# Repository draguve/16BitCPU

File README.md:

A 16 Bit CPU Schematic

## Instruction Set

It can be found [here](https://docs.google.com/spreadsheets/d/1bDObkBc0xerhLb_7aUqUZHJFpincPKz191_meNZrJVs/edit?usp=sharing)

The cpu has 2 Resgisters , an Instruction Register,A Memory Access Register and a simple adder/subtractor and 8Kb RAM and ROM 

*Overview*

*Clock*

*Register*

*Swap-Register*

*ALU*

*Program Counter*

*RAM*

*Control Unit*

*Instruction Register*

*LEDs*

*Display*

*Power*

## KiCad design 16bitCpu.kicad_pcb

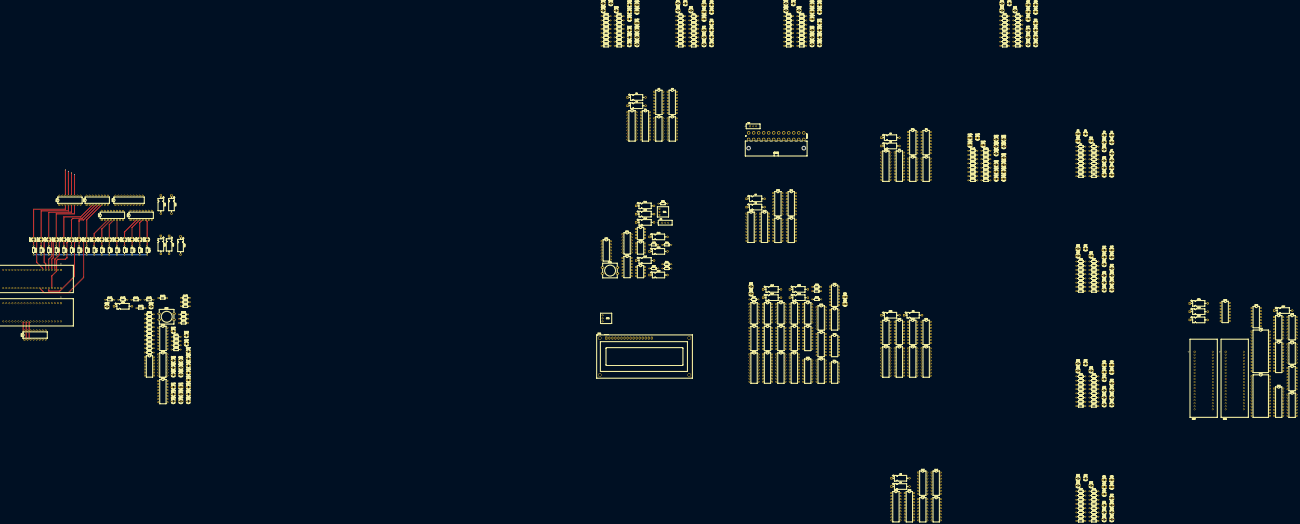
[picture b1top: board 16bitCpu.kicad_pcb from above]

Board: 2 copper layers, 509 parts (0 on the bottom side), 455 nets.

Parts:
C1, C2, C3, C4, C5, C6, C7, C8, C9, C10, C14, C16, C17, C18, C19, C20, C21, C22, C23, C24, C25, C26, C27, C28, C29, C30, C31: 0.1uF; CP_Axial_L10.0mm_D4.5mm_P15.00mm_Horizontal
C11, C13, C15: 0.01uF; CP_Axial_L10.0mm_D4.5mm_P15.00mm_Horizontal
C12: 1uF; CP_Axial_L10.0mm_D4.5mm_P15.00mm_Horizontal
D1, D2, D3, D4, D5, D6, D7, D8, D9, D10, D11, D12, D13, D14, D15, D16, D17, D18, D19, D20, D21, D22, D23, D24, D25, D26, D27, D28, D29, D30, D31, D32, D33, D34, D35, D36, D37, D38, D39, D40, D41, D42, D43, D44, D45, D46, D47, D48, D49, D50, D51, D52, D53, D54, D55, D56, D57, D58, D59, D60, D61, D62, D63, D64, D65, D66, D67, D68, D69, D70, D71, D72, D73, D74, D75, D76, D77, D78, D79, D80, D81, D82, D83, D84, D85, D86, D87, D88, D89, D90, D91, D92, D93, D94, D95, D96, D97, D98, D99, D100, D101, D102, D103, D104, D105, D106, D107, D108, D109, D110, D111, D112, D113, D114, D115, D116, D117, D118, D119, D120, D121, D122, D123, D124, D125, D126, D127, D128, D129, D130, D131, D132, D133, D134, D135, D136, D137, D138, D139, D140, D141, D142, D143, D144, D145, D146, D147, D148, D149, D150, D151, D152, D153, D154, D155, D156, D157, D158, D159, D160, D161, D162, D163, D164, D165, D166, D167, D168, D169, D170, D171, D172, D173, D174, D175, D176, D177, D178, D179, D180, D181, D182, D183, D184, D185, D186, D187, D188, D189: LED; LED_D3.0mm
DS1: WC1602A
J1: ATX24RH; ATX24_RIGHT_ANGLE
R1, R2, R3, R4, R5, R6, R7, R8, R9, R10, R11, R12, R13, R14, R15, R16, R17, R18, R19, R20, R21, R22, R23, R24, R25, R26, R27, R28, R29, R30, R31, R32, R33, R34, R35, R36, R37, R38, R39, R40, R41, R42, R43, R44, R45, R46, R47, R48, R49, R50, R51, R52, R53, R54, R55, R56, R57, R58, R59, R60, R61, R62, R63, R64, R65, R66, R67, R68, R69, R70, R71, R72, R73, R74, R75, R76, R77, R78, R79, R80, R87, R88, R89, R90, R91, R92, R93, R94, R95, R96, R97, R98, R99, R100, R101, R102, R103, R104, R105, R106, R107, R108, R109, R110, R111, R112, R113, R114, R115, R116, R117, R118, R119, R120, R121, R122, R123, R124, R125, R126, R127, R128, R129, R130, R131, R132, R133, R134, R135, R136, R137, R138, R139, R140, R141, R142, R143, R144, R145, R146, R147, R148, R149, R150, R151, R152, R153, R154, R155, R156, R157, R158, R159, R160, R161, R162, R163, R164, R165, R166, R167, R168, R169, R170, R172, R173, R174, R175, R176, R177, R178, R179, R180, R181, R182, R183, R184, R185, R186, R187, R188, R189, R190, R191, R192, R193, R194, R195, R196: 220; R_Axial_DIN0204_L3.6mm_D1.6mm_P7.62mm_Horizontal
R81, R82, R83, R85, R86, R171: 1K; R_Axial_DIN0204_L3.6mm_D1.6mm_P7.62mm_Horizontal
R84: 1M; R_Axial_DIN0204_L3.6mm_D1.6mm_P7.62mm_Horizontal
RV1: 1M; Potentiometer-5.5mm
RV2: 10K; Potentiometer-5.5mm
SW1: SW_Push; SW_PUSH-12mm
SW2: SW_SPDT; SW_MINI-SPDT-SW
SW3: SW_Push-Switch; SW_PUSH-12mm
SW4: SW_SPDT-Switch; SW_MINI-SPDT-SW
U1, U4, U7, U10, U13, U14, U19, U22, U25, U28, U29, U32, U39, U52, U54, U59, U65, U66, U69: 74LS245; DIP-20_W7.62mm
U2, U3, U5, U6, U8, U9, U11, U12, U20, U21, U23, U24, U26, U27, U30, U31, U57, U61, U62, U63, U64, U67, U68, U70, U71: 74LS173; DIP-16_W7.62mm
U15, U16, U17, U18: 74LS161; DIP-16_W7.62mm
U33, U37, U38: LMC555xN; DIP-8_W7.62mm
U34: 74LS04; DIP-14_W7.62mm
U35: 74LS08; DIP-14_W7.62mm
U36: 74LS32; DIP-14_W7.62mm
U40, U44, U47, U48: 74LS00; DIP-14_W7.62mm
U41, U42, U43, U45: 74LS86; DIP-14_W7.62mm
U46: 74HC02; DIP-14_W7.62mm
U49, U51, U55, U58: 74LS283; DIP-16_W7.62mm
U50, U53, U56, U60: 74LS85; DIP-16_W7.62mm
U72, U78: 74HC04; DIP-14_W7.62mm
U73: 74HC00; DIP-14_W7.62mm
U74, U75, U81, U82: AT28C256; ZIF-AT28C64B-15PU
U76, U77: AS6C62256A; DIP-28_W15.24mm
U79: 7400; DIP-14_W7.62mm
U80: 74LS161-74xx; DIP-16_W7.62mm
U83, U84, U85: 74LS138; DIP-16_W7.62mm

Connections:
+5V: C1.1, C2.1, C3.1, C4.1, C5.1, C6.1, C7.1, C8.1, C9.1, C10.1, C16.1, C17.1, C18.1, C19.1, C20.1, C21.1, C22.1, C23.1, C24.1, C25.1, C26.1, C27.1, C28.1, C29.1, C30.1, C31.1, DS1.2, DS1.15, J1.4, R81.1, R83.1, R84.1, R85.1, R86.1, SW3.2, U1.1, U1.20, U2.16, U3.16, U4.1, U4.20, U5.16, U6.16, U7.1, U7.20, U8.16, U9.16, U10.1, U10.20, U11.16, U12.16, U13.1, U13.20, U14.1, U14.20, U15.16, U16.16, U17.16, U18.16, U19.1, U19.20, U20.16, U21.16, U22.1, U22.20, U23.16, U24.16, U25.1, U25.20, U26.16, U27.16, U28.1, U28.20, U29.1, U29.20, U30.16, U31.16, U32.1, U32.20, U33.4, U33.8, U34.14, U35.14, U36.14, U37.4, U37.8, U38.8, U39.1, U39.20, U40.7, U41.14, U42.14, U43.14, U44.7, U45.14, U46.14, U47.7, U48.7, U49.16, U50.16, U51.16, U52.1, U52.20, U53.16, U54.1, U54.20, U55.16, U56.16, U57.16, U58.16, U59.1, U59.20, U60.16, U61.16, U62.16, U63.16, U64.16, U65.1, U65.20, U66.1, U66.20, U67.16, U68.16, U69.1, U69.20, U70.16, U71.16, U72.14, U73.14, U74.28, U75.28, U76.28, U77.28, U79.14, U80.7, U80.9, U80.10, U80.16, U81.28, U82.28, U83.16, U84.6, U84.16, U85.6, U85.16
/ALU/A0: D1.2, U1.2, U2.3, U47.1, U49.5, U50.15
/ALU/A1: D2.2, U1.3, U2.4, U45.3, U47.2, U47.4, U49.3, U49.6, U50.9, U50.13
/ALU/A2: D3.2, U1.4, U2.5, U47.9, U49.14, U50.12
/ALU/A3: D4.2, U1.5, U2.6, U43.6, U47.12, U48.5, U49.12, U50.10, U51.2, U53.11
/ALU/A4: D5.2, U1.6, U3.3, U48.1, U51.5, U53.10
/ALU/A5: D6.2, U1.7, U3.4, U48.4, U51.3, U53.12
/ALU/A6: D7.2, U1.8, U3.5, U48.9, U51.14, U53.13
/ALU/A7: D8.2, U1.9, U3.6, U48.12, U51.12, U53.15
/ALU/A8: D9.2, U4.2, U5.3, U40.1, U55.5, U56.10
/ALU/A9: D10.2, U4.3, U5.4, U40.4, U55.3, U56.12
/ALU/A10: D11.2, U4.4, U5.5, U40.9, U55.14, U56.13
/ALU/A11: D12.2, U4.5, U5.6, U40.12, U55.12, U56.15
/ALU/A12: D13.2, U4.6, U6.3, U44.1, U58.5, U60.10
/ALU/A13: D14.2, U4.7, U6.4, U44.4, U58.3, U60.12
/ALU/A14: D15.2, U4.8, U6.5, U44.9, U58.14, U60.13
/ALU/A15: D16.2, U4.9, U6.6, U44.12, U58.12, U60.15
/ALU/AGTBF: D81.2, U57.3, U81.1, U82.1
/ALU/ALTBF: D82.2, U57.4, U81.26, U82.26
/ALU/BUS0: D133.2, DS1.7, U1.18, U2.14, U7.18, U8.14, U13.18, U15.3, U19.18, U20.14, U25.18, U26.14, U29.18, U52.18, U59.18, U61.14, U65.18, U66.18, U67.14, U74.11, U76.11
/ALU/BUS1: D134.2, DS1.8, U1.17, U2.13, U7.17, U8.13, U13.17, U15.4, U19.17, U20.13, U25.17, U26.13, U29.17, U52.17, U59.17, U61.13, U65.17, U66.17, U67.13, U74.12, U76.12
/ALU/BUS2: D135.2, DS1.9, U1.16, U2.12, U7.16, U8.12, U13.16, U15.5, U19.16, U20.12, U25.16, U26.12, U29.16, U52.16, U59.16, U61.12, U65.16, U66.16, U67.12, U74.13, U76.13
/ALU/BUS3: D136.2, DS1.10, U1.15, U2.11, U7.15, U8.11, U13.15, U15.6, U19.15, U20.11, U25.15, U26.11, U29.15, U52.15, U59.15, U61.11, U65.15, U66.15, U67.11, U74.15, U76.15
/ALU/BUS4: D137.2, DS1.11, U1.14, U3.14, U7.14, U9.14, U13.14, U16.3, U19.14, U21.14, U25.14, U27.14, U29.14, U52.14, U59.14, U62.14, U65.14, U66.14, U68.14, U74.16, U76.16
/ALU/BUS5: D138.2, DS1.12, U1.13, U3.13, U7.13, U9.13, U13.13, U16.4, U19.13, U21.13, U25.13, U27.13, U29.13, U52.13, U59.13, U62.13, U65.13, U66.13, U68.13, U74.17, U76.17
/ALU/BUS6: D139.2, DS1.13, U1.12, U3.12, U7.12, U9.12, U13.12, U16.5, U19.12, U21.12, U25.12, U27.12, U29.12, U52.12, U59.12, U62.12, U65.12, U66.12, U68.12, U74.18, U76.18
/ALU/BUS7: D140.2, DS1.14, U1.11, U3.11, U7.11, U9.11, U13.11, U16.6, U19.11, U21.11, U25.11, U27.11, U29.11, U52.11, U59.11, U62.11, U65.11, U66.11, U68.11, U74.19, U76.19
/ALU/BUS8: D141.2, U4.18, U5.14, U10.18, U11.14, U14.18, U17.3, U22.18, U23.14, U28.18, U30.14, U32.18, U39.18, U54.18, U63.14, U69.18, U70.14, U75.11, U77.11
/ALU/BUS9: D142.2, U4.17, U5.13, U10.17, U11.13, U14.17, U17.4, U22.17, U23.13, U28.17, U30.13, U32.17, U39.17, U54.17, U63.13, U69.17, U70.13, U75.12, U77.12
/ALU/BUS10: D143.2, U4.16, U5.12, U10.16, U11.12, U14.16, U17.5, U22.16, U23.12, U28.16, U30.12, U32.16, U39.16, U54.16, U63.12, U69.16, U70.12, U75.13, U77.13
/ALU/BUS11: D144.2, U4.15, U5.11, U10.15, U11.11, U14.15, U17.6, U22.15, U23.11, U28.15, U30.11, U32.15, U39.15, U54.15, U63.11, U69.15, U70.11, U75.15, U77.15
/ALU/BUS12: D145.2, U4.14, U6.14, U10.14, U12.14, U14.14, U18.3, U22.14, U24.14, U28.14, U31.14, U32.14, U39.14, U54.14, U64.14, U69.14, U71.14, U75.16, U77.16
/ALU/BUS13: D146.2, U4.13, U6.13, U10.13, U12.13, U14.13, U18.4, U22.13, U24.13, U28.13, U31.13, U32.13, U39.13, U54.13, U64.13, U69.13, U71.13, U75.17, U77.17
/ALU/BUS14: D147.2, U4.12, U6.12, U10.12, U12.12, U14.12, U18.5, U22.12, U24.12, U28.12, U31.12, U32.12, U39.12, U54.12, U64.12, U69.12, U71.12, U75.18, U77.18
/ALU/BUS15: D148.2, U4.11, U6.11, U10.11, U12.11, U14.11, U18.6, U22.11, U24.11, U28.11, U31.11, U32.11, U39.11, U54.11, U64.11, U69.11, U71.11, U75.19, U77.19
/ALU/CF: D84.2, U57.6, U81.2, U82.2
/ALU/CLK: U2.7, U3.7, U5.7, U6.7, U8.7, U9.7, U11.7, U12.7, U15.2, U20.7, U21.7, U23.7, U24.7, U26.7, U27.7, U30.7, U31.7, U34.5, U35.8, U57.7, U61.7, U62.7, U63.7, U64.7, U67.7, U68.7, U70.7, U71.7, U72.1, U80.2
/ALU/CLR: U2.15, U3.15, U5.15, U6.15, U8.15, U9.15, U11.15, U12.15, U15.1, U16.1, U17.1, U18.1, U20.15, U21.15, U23.15, U24.15, U26.15, U27.15, U30.15, U31.15, U57.15, U61.15, U62.15, U63.15, U64.15, U67.15, U68.15, U70.15, U71.15, U79.8
/ALU/ZF: D83.2, U57.5, U81.23, U82.23
/ALU/sheet67DDEE7E/I0: D101.2, U47.3, U59.2
/ALU/sheet67DDEE7E/I1: D102.2, U47.6, U59.3
/ALU/sheet67DDEE7E/I2: D103.2, U47.8, U59.4
/ALU/sheet67DDEE7E/I3: D104.2, U47.11, U59.5
/ALU/sheet67DDEE7E/I4: D105.2, U48.3, U59.6
/ALU/sheet67DDEE7E/I5: D106.2, U48.6, U59.7
/ALU/sheet67DDEE7E/I6: D107.2, U48.8, U59.8
/ALU/sheet67DDEE7E/I7: D108.2, U48.11, U59.9
/ALU/sheet67DDEE7E/I8: D109.2, U39.2, U40.3
/ALU/sheet67DDEE7E/I9: D110.2, U39.3, U40.6
/ALU/sheet67DDEE7E/I10: D111.2, U39.4, U40.8
/ALU/sheet67DDEE7E/I11: D112.2, U39.5, U40.11
/ALU/sheet67DDEE7E/I12: D113.2, U39.6, U44.3
/ALU/sheet67DDEE7E/I13: D114.2, U39.7, U44.6
/ALU/sheet67DDEE7E/I14: D115.2, U39.8, U44.8
/ALU/sheet67DDEE7E/I15: D116.2, U39.9, U44.11
/ALU/sheet61054F43/I0: D85.2, U49.4, U52.2
/ALU/sheet61054F43/I1: D86.2, U49.1, U52.3
/ALU/sheet61054F43/I2: D87.2, U49.13, U52.4
/ALU/sheet61054F43/I3: D88.2, U49.10, U52.5
/ALU/sheet61054F43/I4: D89.2, U51.4, U52.6
/ALU/sheet61054F43/I5: D90.2, U51.1, U52.7
/ALU/sheet61054F43/I6: D91.2, U51.13, U52.8
/ALU/sheet61054F43/I7: D92.2, U51.10, U52.9
/ALU/sheet61054F43/I8: D93.2, U54.2, U55.4
/ALU/sheet61054F43/I9: D94.2, U54.3, U55.1
/ALU/sheet61054F43/I10: D95.2, U54.4, U55.13
/ALU/sheet61054F43/I11: D96.2, U54.5, U55.10
/ALU/sheet61054F43/I12: D97.2, U54.6, U58.4
/ALU/sheet61054F43/I13: D98.2, U54.7, U58.1
/ALU/sheet61054F43/I14: D99.2, U54.8, U58.13
/ALU/sheet61054F43/I15: D100.2, U54.9, U58.10
/Control-Unit/ALU_SU: D169.2, U41.2, U41.5, U41.10, U41.13, U42.2, U42.5, U42.10, U42.13, U43.2, U43.5, U43.10, U43.13, U45.2, U45.5, U45.10, U45.13, U49.7, U82.13
/Control-Unit/DSP_E: D172.2, DS1.6, U82.17
/Control-Unit/DSP_RS: D170.2, DS1.4, U82.15
/Control-Unit/DSP_R\W: D171.2, DS1.5, U82.16
/Control-Unit/I0: D117.2, U61.3, U81.7, U82.7
/Control-Unit/I1: D118.2, U61.4, U81.6, U82.6
/Control-Unit/I2: D119.2, U61.5, U81.5, U82.5
/Control-Unit/I3: D120.2, U61.6, U81.4, U82.4
/Control-Unit/I4: D121.2, U62.3, U81.3, U82.3
/Control-Unit/I5: D122.2, U62.4, U81.25, U82.25
/Control-Unit/I6: D123.2, U62.5, U81.24, U82.24
/Control-Unit/I7: D124.2, U62.6, U81.21, U82.21
/Control-Unit/RESET_COUNTER: D165.2, U79.2, U82.19
/Control-Unit/~ALU_EO: D181.2, U52.19, U54.19, U84.13
/Control-Unit/~ALU_FI: D168.2, U57.9, U57.10, U82.12
/Control-Unit/~ALU_NAND_O: D182.2, U39.19, U59.19, U84.12
/Control-Unit/~CLR: U79.1, U79.9, U79.10, U79.11
/Control-Unit/~HLT: U35.10, U84.7
/Control-Unit/~SI: D189.2, U20.9, U20.10, U21.9, U21.10, U23.9, U23.10, U24.9, U24.10, U85.7
/Control-Unit/~SO: D179.2, U19.19, U22.19, U83.7
/Control-Unit/~XI: D188.2, U26.9, U26.10, U27.9, U27.10, U30.9, U30.10, U31.9, U31.10, U85.9
/Control-Unit/~XO: D178.2, U25.19, U28.19, U83.9
/Control-Unit/~X_SWP_O: U29.19, U32.19, U84.11
/Instruction-Register/sheet621E2544/I8: D125.2, U63.3, U65.2
/Instruction-Register/sheet621E2544/I9: D126.2, U63.4, U65.3
/Instruction-Register/sheet621E2544/I10: D127.2, U63.5, U65.4
/Instruction-Register/sheet621E2544/I11: D128.2, U63.6, U65.5
/Instruction-Register/sheet621E2544/I12: D129.2, U64.3, U65.6
/Instruction-Register/sheet621E2544/I13: D130.2, U64.4, U65.7
/Instruction-Register/sheet621E2544/I14: D131.2, U64.5, U65.8
/Instruction-Register/sheet621E2544/I15: D132.2, U64.6, U65.9
/Instruction-Register/~I80: D177.2, U65.19, U83.10
/Instruction-Register/~II: D187.2, U61.9, U61.10, U62.9, U62.10, U63.9, U63.10, U64.9, U64.10, U85.10
/ProgramCounter/CE: D167.2, U15.7, U15.10, U16.7, U16.10, U17.7, U17.10, U18.7, U18.10, U82.11
/ProgramCounter/sheet6156E9A4/I0: D33.2, U13.2, U15.14
/ProgramCounter/sheet6156E9A4/I1: D34.2, U13.3, U15.13
/ProgramCounter/sheet6156E9A4/I2: D35.2, U13.4, U15.12
/ProgramCounter/sheet6156E9A4/I3: D36.2, U13.5, U15.11
/ProgramCounter/sheet6156E9A4/I4: D37.2, U13.6, U16.14
/ProgramCounter/sheet6156E9A4/I5: D38.2, U13.7, U16.13
/ProgramCounter/sheet6156E9A4/I6: D39.2, U13.8, U16.12
/ProgramCounter/sheet6156E9A4/I7: D40.2, U13.9, U16.11
/ProgramCounter/sheet6156E9A4/I8: D41.2, U14.2, U17.14
/ProgramCounter/sheet6156E9A4/I9: D42.2, U14.3, U17.13
/ProgramCounter/sheet6156E9A4/I10: D43.2, U14.4, U17.12
/ProgramCounter/sheet6156E9A4/I11: D44.2, U14.5, U17.11
/ProgramCounter/sheet6156E9A4/I12: D45.2, U14.6, U18.14
/ProgramCounter/sheet6156E9A4/I13: D46.2, U14.7, U18.13
/ProgramCounter/sheet6156E9A4/I14: D47.2, U14.8, U18.12
/ProgramCounter/sheet6156E9A4/I15: D48.2, U14.9, U18.11
/ProgramCounter/~CO: D176.2, U13.19, U14.19, U83.11
/ProgramCounter/~J: D186.2, U15.9, U16.9, U17.9, U18.9, U85.11
/RAM/MEMWE: D166.2, U73.1, U81.19
/RAM/sheet61B5B12C/I0: D149.2, U66.2, U67.3, U74.10, U75.10, U76.10, U77.10
/RAM/sheet61B5B12C/I1: D150.2, U66.3, U67.4, U74.9, U75.9, U76.9, U77.9
/RAM/sheet61B5B12C/I2: D151.2, U66.4, U67.5, U74.8, U75.8, U76.8, U77.8
/RAM/sheet61B5B12C/I3: D152.2, U66.5, U67.6, U74.7, U75.7, U76.7, U77.7
/RAM/sheet61B5B12C/I4: D153.2, U66.6, U68.3, U74.6, U75.6, U76.6, U77.6
/RAM/sheet61B5B12C/I5: D154.2, U66.7, U68.4, U74.5, U75.5, U76.5, U77.5
/RAM/sheet61B5B12C/I6: D155.2, U66.8, U68.5, U74.4, U75.4, U76.4, U77.4
/RAM/sheet61B5B12C/I7: D156.2, U66.9, U68.6, U74.3, U75.3, U76.3, U77.3
/RAM/sheet61B5B12C/I8: D157.2, U69.2, U70.3, U74.25, U75.25, U76.25, U77.25
/RAM/sheet61B5B12C/I9: D158.2, U69.3, U70.4, U74.24, U75.24, U76.24, U77.24
/RAM/sheet61B5B12C/I10: D159.2, U69.4, U70.5, U74.21, U75.21, U76.21, U77.21
/RAM/sheet61B5B12C/I11: D160.2, U69.5, U70.6, U74.23, U75.23, U76.23, U77.23
/RAM/sheet61B5B12C/I12: D161.2, U69.6, U71.3, U74.2, U75.2, U76.2, U77.2
/RAM/sheet61B5B12C/I13: D162.2, U69.7, U71.4, U74.26, U75.26, U76.26, U77.26
/RAM/sheet61B5B12C/I14: D163.2, U69.8, U71.5, U74.1, U75.1, U76.1, U77.1
/RAM/sheet61B5B12C/I15: D164.2, U69.9, U71.6, U74.20, U75.20, U78.1
/RAM/~AI: D185.2, U67.9, U67.10, U68.9, U68.10, U70.9, U70.10, U71.9, U71.10, U85.12
/RAM/~AO: D175.2, U66.19, U69.19, U83.12
/RAM/~MEMOE: D180.2, U74.22, U75.22, U76.22, U77.22, U84.14
/Register-A/~AI: D183.2, U2.9, U2.10, U3.9, U3.10, U5.9, U5.10, U6.9, U6.10, U85.14
/Register-A/~AO: D173.2, U1.19, U4.19, U83.14
/Register-B/A0: D17.2, U7.2, U8.3, U45.1
/Register-B/A1: D18.2, U7.3, U8.4, U45.4
/Register-B/A2: D19.2, U7.4, U8.5, U45.9
/Register-B/A3: D20.2, U7.5, U8.6, U45.12
/Register-B/A4: D21.2, U7.6, U9.3, U43.1
/Register-B/A5: D22.2, U7.7, U9.4, U43.4
/Register-B/A6: D23.2, U7.8, U9.5, U43.9
/Register-B/A7: D24.2, U7.9, U9.6, U43.12
/Register-B/A8: D25.2, U10.2, U11.3, U42.1
/Register-B/A9: D26.2, U10.3, U11.4, U42.4
/Register-B/A10: D27.2, U10.4, U11.5, U42.9
/Register-B/A11: D28.2, U10.5, U11.6, U42.12
/Register-B/A12: D29.2, U10.6, U12.3, U41.1
/Register-B/A13: D30.2, U10.7, U12.4, U41.4
/Register-B/A14: D31.2, U10.8, U12.5, U41.9
/Register-B/A15: D32.2, U10.9, U12.6, U41.12
/Register-B/~AI: D184.2, U8.9, U8.10, U9.9, U9.10, U11.9, U11.10, U12.9, U12.10, U85.13
/Register-B/~AO: D174.2, U7.19, U10.19, U83.13
/Sheet61DF6CC6/sheet623AC6D9/I0: D65.2, U25.2, U26.3, U32.2
/Sheet61DF6CC6/sheet623AC6D9/I1: D66.2, U25.3, U26.4, U32.3
/Sheet61DF6CC6/sheet623AC6D9/I2: D67.2, U25.4, U26.5, U32.4
/Sheet61DF6CC6/sheet623AC6D9/I3: D68.2, U25.5, U26.6, U32.5
/Sheet61DF6CC6/sheet623AC6D9/I4: D69.2, U25.6, U27.3, U32.6
/Sheet61DF6CC6/sheet623AC6D9/I5: D70.2, U25.7, U27.4, U32.7
/Sheet61DF6CC6/sheet623AC6D9/I6: D71.2, U25.8, U27.5, U32.8
/Sheet61DF6CC6/sheet623AC6D9/I7: D72.2, U25.9, U27.6, U32.9
/Sheet61DF6CC6/sheet623AC6D9/I8: D73.2, U28.2, U29.2, U30.3
/Sheet61DF6CC6/sheet623AC6D9/I9: D74.2, U28.3, U29.3, U30.4
/Sheet61DF6CC6/sheet623AC6D9/I10: D75.2, U28.4, U29.4, U30.5
/Sheet61DF6CC6/sheet623AC6D9/I11: D76.2, U28.5, U29.5, U30.6
/Sheet61DF6CC6/sheet623AC6D9/I12: D77.2, U28.6, U29.6, U31.3
/Sheet61DF6CC6/sheet623AC6D9/I13: D78.2, U28.7, U29.7, U31.4
/Sheet61DF6CC6/sheet623AC6D9/I14: D79.2, U28.8, U29.8, U31.5
/Sheet61DF6CC6/sheet623AC6D9/I15: D80.2, U28.9, U29.9, U31.6
/Stack/sheet60C9B368/I0: D49.2, U19.2, U20.3
/Stack/sheet60C9B368/I1: D50.2, U19.3, U20.4
/Stack/sheet60C9B368/I2: D51.2, U19.4, U20.5
/Stack/sheet60C9B368/I3: D52.2, U19.5, U20.6
/Stack/sheet60C9B368/I4: D53.2, U19.6, U21.3
/Stack/sheet60C9B368/I5: D54.2, U19.7, U21.4
/Stack/sheet60C9B368/I6: D55.2, U19.8, U21.5
/Stack/sheet60C9B368/I7: D56.2, U19.9, U21.6
/Stack/sheet60C9B368/I8: D57.2, U22.2, U23.3
/Stack/sheet60C9B368/I9: D58.2, U22.3, U23.4
/Stack/sheet60C9B368/I10: D59.2, U22.4, U23.5
/Stack/sheet60C9B368/I11: D60.2, U22.5, U23.6
/Stack/sheet60C9B368/I12: D61.2, U22.6, U24.3
/Stack/sheet60C9B368/I13: D62.2, U22.7, U24.4
/Stack/sheet60C9B368/I14: D63.2, U22.8, U24.5
/Stack/sheet60C9B368/I15: D64.2, U22.9, U24.6
GND: C1.2, C2.2, C3.2, C4.2, C5.2, C6.2, C7.2, C8.2, C9.2, C10.2, C11.2, C12.2, C13.2, C14.2, C15.2, C16.2, C17.2, C18.2, C19.2, C20.2, C21.2, C22.2, C23.2, C24.2, C25.2, C26.2, C27.2, C28.2, C29.2, C30.2, C31.2, DS1.1, DS1.16, J1.5, R1.2, R2.2, R3.2, R4.2, R5.2, R6.2, R7.2, R8.2, R9.2, R10.2, R11.2, R12.2, R13.2, R14.2, R15.2, R16.2, R17.2, R18.2, R19.2, R20.2, R21.2, R22.2, R23.2, R24.2, R25.2, R26.2, R27.2, R28.2, R29.2, R30.2, R31.2, R32.2, R33.2, R34.2, R35.2, R36.2, R37.2, R38.2, R39.2, R40.2, R41.2, R42.2, R43.2, R44.2, R45.2, R46.2, R47.2, R48.2, R49.2, R50.2, R51.2, R52.2, R53.2, R54.2, R55.2, R56.2, R57.2, R58.2, R59.2, R60.2, R61.2, R62.2, R63.2, R64.2, R65.2, R66.2, R67.2, R68.2, R69.2, R70.2, R71.2, R72.2, R73.2, R74.2, R75.2, R76.2, R77.2, R78.2, R79.2, R80.2, R87.2, R88.2, R89.2, R90.2, R91.2, R92.2, R93.2, R94.2, R95.2, R96.2, R97.2, R98.2, R99.2, R100.2, R101.2, R102.2, R103.2, R104.2, R105.2, R106.2, R107.2, R108.2, R109.2, R110.2, R111.2, R112.2, R113.2, R114.2, R115.2, R116.2, R117.2, R118.2, R119.2, R120.2, R121.2, R122.2, R123.2, R124.2, R125.2, R126.2, R127.2, R128.2, R129.2, R130.2, R131.2, R132.2, R133.2, R134.2, R135.2, R136.2, R137.2, R138.2, R139.2, R140.2, R141.2, R142.2, R143.2, R144.2, R145.2, R146.2, R147.2, R148.2, R149.2, R150.2, R151.2, R152.2, R153.2, R154.2, R155.2, R156.2, R157.2, R158.2, R159.2, R160.2, R161.2, R162.2, R163.2, R164.2, R165.2, R166.2, R167.2, R168.2, R169.2, R170.2, R171.2, R172.2, R173.2, R174.2, R175.2, R176.2, R177.2, R178.2, R179.2, R180.2, R181.2, R182.2, R183.2, R184.2, R185.2, R186.2, R187.2, R188.2, R189.2, R190.2, R191.2, R192.2, R193.2, R194.2, R195.2, R196.2, RV2.1, SW1.1, SW2.2, U1.10, U2.1, U2.2, U2.8, U3.1, U3.2, U3.8, U4.10, U5.1, U5.2, U5.8, U6.1, U6.2, U6.8, U7.10, U8.1, U8.2, U8.8, U9.1, U9.2, U9.8, U10.10, U11.1, U11.2, U11.8, U12.1, U12.2, U12.8, U13.10, U14.10, U15.8, U16.8, U17.8, U18.8, U19.10, U20.1, U20.2, U20.8, U21.1, U21.2, U21.8, U22.10, U23.1, U23.2, U23.8, U24.1, U24.2, U24.8, U25.10, U26.1, U26.2, U26.8, U27.1, U27.2, U27.8, U28.10, U29.10, U30.1, U30.2, U30.8, U31.1, U31.2, U31.8, U32.10, U33.1, U34.7, U35.7, U36.7, U37.1, U38.1, U38.6, U39.10, U40.14, U41.7, U42.7, U43.7, U44.14, U45.7, U46.7, U47.14, U48.14, U49.8, U50.8, U51.8, U52.10, U53.8, U54.10, U55.8, U56.8, U57.1, U57.2, U57.8, U58.8, U59.10, U60.8, U61.1, U61.2, U61.8, U62.1, U62.2, U62.8, U63.1, U63.2, U63.8, U64.1, U64.2, U64.8, U65.10, U66.10, U67.1, U67.2, U67.8, U68.1, U68.2, U68.8, U69.10, U70.1, U70.2, U70.8, U71.1, U71.2, U71.8, U72.7, U73.7, U74.14, U75.14, U76.14, U77.14, U79.7, U80.8, U81.14, U81.20, U81.22, U82.14, U82.20, U82.22, U83.4, U83.5, U83.8, U84.4, U84.8, U85.4, U85.5, U85.8
unnamed: C11.1, U33.5
unnamed: C12.1, RV1.1, U33.2, U33.6
unnamed: C13.1, U37.5
unnamed: C14.1, R84.2, U37.6, U37.7
unnamed: C15.1, U38.5
unnamed: D1.1, R1.1
unnamed: D2.1, R2.1
unnamed: D3.1, R3.1
unnamed: D4.1, R4.1
unnamed: D5.1, R5.1
unnamed: D6.1, R6.1
unnamed: D7.1, R7.1
unnamed: D8.1, R8.1
unnamed: D9.1, R9.1
unnamed: D10.1, R10.1
unnamed: D11.1, R11.1
unnamed: D12.1, R12.1
unnamed: D13.1, R13.1
unnamed: D14.1, R14.1
unnamed: D15.1, R15.1
unnamed: D16.1, R16.1
unnamed: D17.1, R17.1
unnamed: D18.1, R18.1
unnamed: D19.1, R19.1
unnamed: D20.1, R20.1
unnamed: D21.1, R21.1
unnamed: D22.1, R22.1
unnamed: D23.1, R23.1
unnamed: D24.1, R24.1
unnamed: D25.1, R25.1
unnamed: D26.1, R26.1
unnamed: D27.1, R27.1
unnamed: D28.1, R28.1
unnamed: D29.1, R29.1
unnamed: D30.1, R30.1
unnamed: D31.1, R31.1
unnamed: D32.1, R32.1
unnamed: D33.1, R33.1
unnamed: D34.1, R34.1
unnamed: D35.1, R35.1
unnamed: D36.1, R36.1
unnamed: D37.1, R37.1
unnamed: D38.1, R38.1
unnamed: D39.1, R39.1
unnamed: D40.1, R40.1
unnamed: D41.1, R41.1
unnamed: D42.1, R42.1
unnamed: D43.1, R43.1
unnamed: D44.1, R44.1
unnamed: D45.1, R45.1
unnamed: D46.1, R46.1
unnamed: D47.1, R47.1
unnamed: D48.1, R48.1
unnamed: D49.1, R49.1
unnamed: D50.1, R50.1
unnamed: D51.1, R51.1
unnamed: D52.1, R52.1
unnamed: D53.1, R53.1
unnamed: D54.1, R54.1
unnamed: D55.1, R55.1
unnamed: D56.1, R56.1
unnamed: D57.1, R57.1
unnamed: D58.1, R58.1
unnamed: D59.1, R59.1
unnamed: D60.1, R60.1
unnamed: D61.1, R61.1
unnamed: D62.1, R62.1
unnamed: D63.1, R63.1
unnamed: D64.1, R64.1
unnamed: D65.1, R65.1
unnamed: D66.1, R66.1
unnamed: D67.1, R67.1
unnamed: D68.1, R68.1
unnamed: D69.1, R69.1
unnamed: D70.1, R70.1
unnamed: D71.1, R71.1
unnamed: D72.1, R72.1
unnamed: D73.1, R73.1
unnamed: D74.1, R74.1
unnamed: D75.1, R75.1
unnamed: D76.1, R76.1
unnamed: D77.1, R77.1
unnamed: D78.1, R78.1
unnamed: D79.1, R79.1
unnamed: D80.1, R80.1
unnamed: D81.1, R87.1
unnamed: D82.1, R88.1
unnamed: D83.1, R89.1
unnamed: D84.1, R90.1
unnamed: D85.1, R91.1
unnamed: D86.1, R92.1
unnamed: D87.1, R93.1
unnamed: D88.1, R94.1
unnamed: D89.1, R95.1
unnamed: D90.1, R96.1
unnamed: D91.1, R97.1
unnamed: D92.1, R98.1
unnamed: D93.1, R99.1
unnamed: D94.1, R100.1
unnamed: D95.1, R101.1
unnamed: D96.1, R102.1
unnamed: D97.1, R103.1
unnamed: D98.1, R104.1
unnamed: D99.1, R105.1
unnamed: D100.1, R106.1
unnamed: D101.1, R107.1
unnamed: D102.1, R108.1
unnamed: D103.1, R109.1
unnamed: D104.1, R110.1
unnamed: D105.1, R111.1
unnamed: D106.1, R112.1
unnamed: D107.1, R113.1
unnamed: D108.1, R114.1
unnamed: D109.1, R115.1
unnamed: D110.1, R116.1
unnamed: D111.1, R117.1
unnamed: D112.1, R118.1
unnamed: D113.1, R119.1
unnamed: D114.1, R120.1
unnamed: D115.1, R121.1
unnamed: D116.1, R122.1
unnamed: D117.1, R123.1
unnamed: D118.1, R124.1
unnamed: D119.1, R125.1
unnamed: D120.1, R126.1
unnamed: D121.1, R127.1
unnamed: D122.1, R128.1
unnamed: D123.1, R129.1
unnamed: D124.1, R130.1
unnamed: D125.1, R131.1
unnamed: D126.1, R132.1
unnamed: D127.1, R133.1
unnamed: D128.1, R134.1
unnamed: D129.1, R135.1
unnamed: D130.1, R136.1
unnamed: D131.1, R137.1
unnamed: D132.1, R138.1
unnamed: D133.1, R139.1
unnamed: D134.1, R140.1
unnamed: D135.1, R141.1
unnamed: D136.1, R142.1
unnamed: D137.1, R143.1
unnamed: D138.1, R144.1
unnamed: D139.1, R145.1
unnamed: D140.1, R146.1
unnamed: D141.1, R147.1
unnamed: D142.1, R148.1
unnamed: D143.1, R149.1
unnamed: D144.1, R150.1
unnamed: D145.1, R151.1
unnamed: D146.1, R152.1
unnamed: D147.1, R153.1
unnamed: D148.1, R154.1
unnamed: D149.1, R155.1
unnamed: D150.1, R156.1
unnamed: D151.1, R157.1
unnamed: D152.1, R158.1
unnamed: D153.1, R159.1
unnamed: D154.1, R160.1
unnamed: D155.1, R161.1
unnamed: D156.1, R162.1
unnamed: D157.1, R163.1
unnamed: D158.1, R164.1
unnamed: D159.1, R165.1
unnamed: D160.1, R166.1
unnamed: D161.1, R167.1
unnamed: D162.1, R168.1
unnamed: D163.1, R169.1
unnamed: D164.1, R170.1
unnamed: D165.1, R172.1
unnamed: D166.1, R173.1
unnamed: D167.1, R174.1
unnamed: D168.1, R175.1
unnamed: D169.1, R176.1
unnamed: D170.1, R177.1
unnamed: D171.1, R178.1
unnamed: D172.1, R179.1
unnamed: D173.1, R180.1
unnamed: D174.1, R181.1
unnamed: D175.1, R182.1
unnamed: D176.1, R183.1
unnamed: D177.1, R184.1
unnamed: D178.1, R185.1
unnamed: D179.1, R186.1
unnamed: D180.1, R187.1
unnamed: D181.1, R188.1
unnamed: D182.1, R189.1
unnamed: D183.1, R190.1
unnamed: D184.1, R191.1
unnamed: D185.1, R192.1
unnamed: D186.1, R193.1
unnamed: D187.1, R194.1
unnamed: D188.1, R195.1
unnamed: D189.1, R196.1
unnamed: DS1.3, RV2.2
unnamed: J1.3, SW4.3
unnamed: J1.16, SW4.2
unnamed: R81.2, R82.1, U33.7
unnamed: R82.2, RV1.2
unnamed: R83.2, SW1.2, U37.2
unnamed: R85.2, SW2.1, U38.2
unnamed: R86.2, SW2.3, U38.4
unnamed: R171.1, SW3.1, U79.12, U79.13
unnamed: U15.15, U16.2
unnamed: U16.15, U17.2
unnamed: U17.15, U18.2
unnamed: U33.3, U35.1
unnamed: U34.1, U35.2, U38.3
unnamed: U34.2, U35.4
unnamed: U35.3, U36.1
unnamed: U35.5, U37.3
unnamed: U35.6, U36.2
unnamed: U35.9, U36.3
unnamed: U40.2, U42.3, U55.6, U56.9
unnamed: U40.5, U42.6, U55.2, U56.11
unnamed: U40.10, U42.8, U55.15, U56.14
unnamed: U40.13, U42.11, U55.11, U56.1
unnamed: U41.3, U44.2, U58.6, U60.9
unnamed: U41.6, U44.5, U58.2, U60.11
unnamed: U41.8, U44.10, U58.15, U60.14
unnamed: U41.11, U44.13, U58.11, U60.1
unnamed: U43.3, U48.2, U51.6, U53.9
unnamed: U43.8, U48.10, U51.15, U53.14
unnamed: U43.11, U48.13, U51.11, U53.1
unnamed: U45.6, U47.5, U49.2, U50.11
unnamed: U45.8, U47.10, U49.15, U50.14
unnamed: U45.11, U47.13, U49.11, U50.1
unnamed: U49.9, U51.7
unnamed: U50.5, U53.3
unnamed: U50.6, U53.4
unnamed: U50.7, U53.2
unnamed: U51.9, U55.7
unnamed: U53.5, U56.4
unnamed: U53.6, U56.3
unnamed: U53.7, U56.2
unnamed: U55.9, U58.7
unnamed: U56.5, U60.4
unnamed: U56.6, U60.3
unnamed: U56.7, U60.2
unnamed: U57.11, U58.9
unnamed: U57.12, U60.6
unnamed: U57.13, U60.7
unnamed: U57.14, U60.5
unnamed: U72.2, U72.3
unnamed: U72.4, U73.2
unnamed: U73.3, U76.27, U77.27
unnamed: U76.20, U77.20, U78.2
unnamed: U79.3, U79.4, U79.5
unnamed: U79.6, U80.1
unnamed: U80.12, U81.10, U82.10
unnamed: U80.13, U81.9, U82.9
unnamed: U80.14, U81.8, U82.8
unnamed: U81.11, U83.1, U84.1
unnamed: U81.12, U83.2, U84.2
unnamed: U81.13, U83.3, U84.3
unnamed: U81.15, U83.6, U84.5
unnamed: U81.16, U85.1
unnamed: U81.17, U85.2
unnamed: U81.18, U85.3

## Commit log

2020-09-18 Init , has registers and alu
2020-09-18 Added clock
2020-09-20 make the ram sch
2020-09-20 ram connected,need to add and a cap
2020-09-22 Added the program counter
2020-09-27 Added ROM with 2 inverter cap nonsense
2020-09-27 Added footprints
2020-09-27 Added IR,Cu started
2020-09-27 Fixed power for multi part comps
2020-09-28 Various Fixes
2020-09-28 Fixed ZIF
2020-09-29 Added GND and PWR in ALU and removed the Error
2020-09-29 Added link for Truth Table
2020-10-02 made the CU , need to change the IR
2020-10-11 Register name change
2020-10-12 changed ir to only hold 12
2020-10-12 non floating ram and ir , added stack register
2020-10-12 Added X register
2020-10-12 annotations
2020-10-13 Made IR & Stack 12 bits
2020-10-14 back to 13 bit addresses
2020-10-14 Added 8 bit output to the ir
2020-10-16 Let there be light
2020-10-16 Fixes
2020-10-16 Clean uP
2020-10-18 better alu :
2020-10-18 Added NAND GATES in ALU
2020-10-18 added 3-8 decoders to cu
2020-10-18 removed unneeded chips from the IR
2020-10-18 total fixes
2020-10-18 using new RAM and ROM,15bits baby
2020-10-18 using new ROM in CU and more jumps
2020-10-18 fixed almost all errors
2020-10-18 fixed more errors
2020-10-18 backup
2020-10-18 added images,fixed readme,renamed stuff to not include spaces
2020-10-19 added timer.lib and using correct 555 timer
2020-10-19 clk fix:
2020-10-23 added power caps
2020-10-24 Added power connector
2020-10-24 added display
2020-10-24 images and pcb
2020-10-24 added swp_x, and cleanup readme
2020-10-24 test
